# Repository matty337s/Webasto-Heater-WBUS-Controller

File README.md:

# Webasto Heater WBUS Controller

Controller for webasto heater used in vehicles such as Land Rover Discovery 3. Used to turn on and off heater using ATTINY microcontroller, with inputs for USB, ignition and low-beam. Ignition and low-beam inputs can be used to control the heater using the standard vehicle remote control using programmed sequences. PCB designed for Hammond 1551HFLBK enclosure. Software coming soon.

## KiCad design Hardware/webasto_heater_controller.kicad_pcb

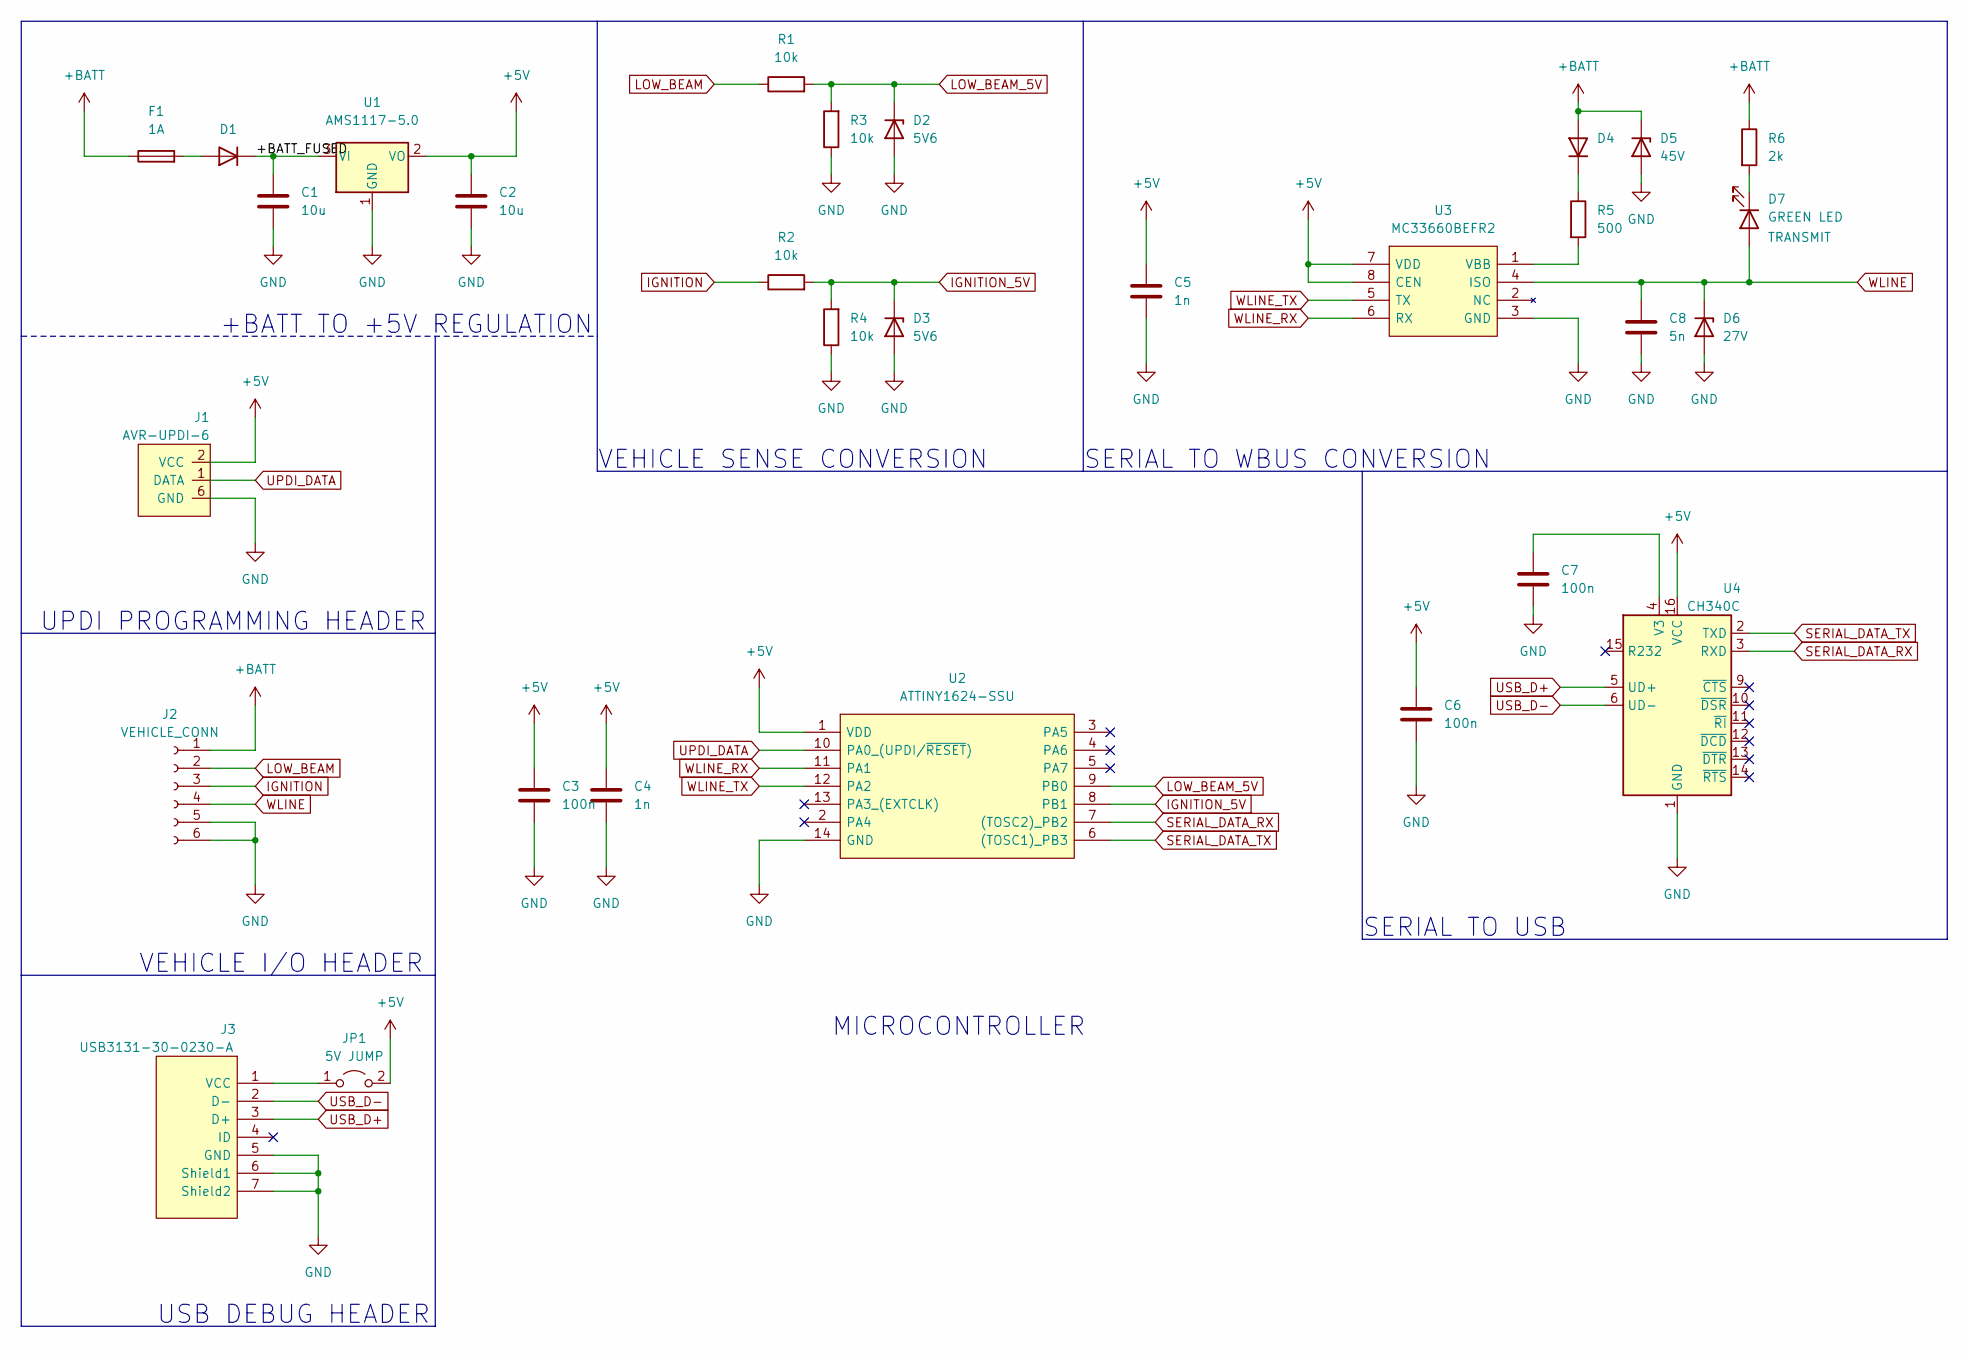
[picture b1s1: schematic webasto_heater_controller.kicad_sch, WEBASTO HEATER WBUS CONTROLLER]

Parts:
C1, C2: 10u; C_0805_2012Metric_Pad1.18x1.45mm_HandSolder
C3, C6, C7: 100n; C_0805_2012Metric_Pad1.18x1.45mm_HandSolder
C4, C5: 1n; C_0805_2012Metric_Pad1.18x1.45mm_HandSolder
C8: 5n; C_0805_2012Metric_Pad1.18x1.45mm_HandSolder
D1, D4: D; D_SOD-323_HandSoldering
D2, D3: 5V6; D_SOD-323_HandSoldering
D5: 45V; D_SOD-323_HandSoldering
D6: 27V; D_SOD-323_HandSoldering
D7: GREEN LED; LED_0805_2012Metric_Pad1.15x1.40mm_HandSolder
F1: 1A; Fuse_0805_2012Metric_Pad1.15x1.40mm_HandSolder
J1: AVR-UPDI-6; PinHeader_2x03_P2.54mm_Vertical
J2: VEHICLE_CONN; PinSocket_1x06_P2.54mm_Horizontal
J3: USB3131-30-0230-A; USB3131300230A; Manufacturer_Part_Number USB3131-30-0230-A; Mouser Part Number 640-USB3131300230A
JP1: 5V JUMP; PinHeader_1x02_P2.54mm_Vertical
R1, R2, R3, R4: 10k; R_0805_2012Metric_Pad1.20x1.40mm_HandSolder
R5: 500; R_0805_2012Metric_Pad1.20x1.40mm_HandSolder
R6: 2k; R_0805_2012Metric_Pad1.20x1.40mm_HandSolder
U1: AMS1117-5.0; SOT-223-3_TabPin2
U2: ATTINY1624-SSU; SOIC127P600X175-14N; Manufacturer_Part_Number ATTINY1624-SSU; Mouser Part Number 556-ATTINY1624-SSU
U3: MC33660BEFR2; SOIC127P600X175-8N; Manufacturer_Part_Number MC33660BEFR2; Mouser Part Number 841-MC33660BEFR2
U4: CH340C; SOIC-16_3.9x9.9mm_P1.27mm

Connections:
+5V: C2.1, C3.1, C4.1, C5.1, C6.1, J1.2 (VCC), JP1.2 (B), U1.2 (VO), U2.1 (VDD), U3.7 (VDD), U3.8 (CEN), U4.16 (VCC)
+BATT: D4.2 (A), D5.1 (K), F1.1, J2.1, R6.1
/+BATT_FUSED: C1.1, D1.1 (K), U1.3 (VI)
GND: C1.2, C2.2, C3.2, C4.2, C5.2, C6.2, C7.2, C8.2, D2.2 (A), D3.2 (A), D5.2 (A), D6.2 (A), J1.6 (GND), J2.5, J2.6, J3.5 (GND), J3.6 (Shield1), J3.7 (Shield2), R3.1, R4.1, U1.1 (GND), U2.14 (GND), U3.3 (GND), U4.1 (GND)
IGNITION: J2.3, R2.1
IGNITION_5V: D3.1 (K), R2.2, R4.2, U2.8 (PB1)
LOW_BEAM: J2.2, R1.1
LOW_BEAM_5V: D2.1 (K), R1.2, R3.2, U2.9 (PB0)
unnamed: C7.1, U4.4 (V3)
unnamed: D1.2 (A), F1.2
unnamed: D4.1 (K), R5.1
unnamed: D7.1 (K), R6.2
unnamed: J3.1 (VCC), JP1.1 (A)
unnamed: R5.2, U3.1 (VBB)
SERIAL_DATA_RX: U2.7 ((TOSC2)_PB2), U4.3 (RXD)
SERIAL_DATA_TX: U2.6 ((TOSC1)_PB3), U4.2 (TXD)
UPDI_DATA: J1.1 (DATA), U2.10 (PA0_(UPDI/~RESET))
USB_D+: J3.3 (D+), U4.5 (UD+)
USB_D-: J3.2 (D-), U4.6 (UD-)
WLINE: C8.1, D6.1 (K), D7.2 (A), J2.4, U3.4 (ISO)
WLINE_RX: U2.11 (PA1), U3.6 (RX)
WLINE_TX: U2.12 (PA2), U3.5 (TX)

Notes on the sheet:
UPDI PROGRAMMING HEADER
+BATT TO +5V REGULATION
SERIAL TO USB
MICROCONTROLLER
USB DEBUG HEADER
VEHICLE I/O HEADER
VEHICLE SENSE CONVERSION
SERIAL TO WBUS CONVERSION

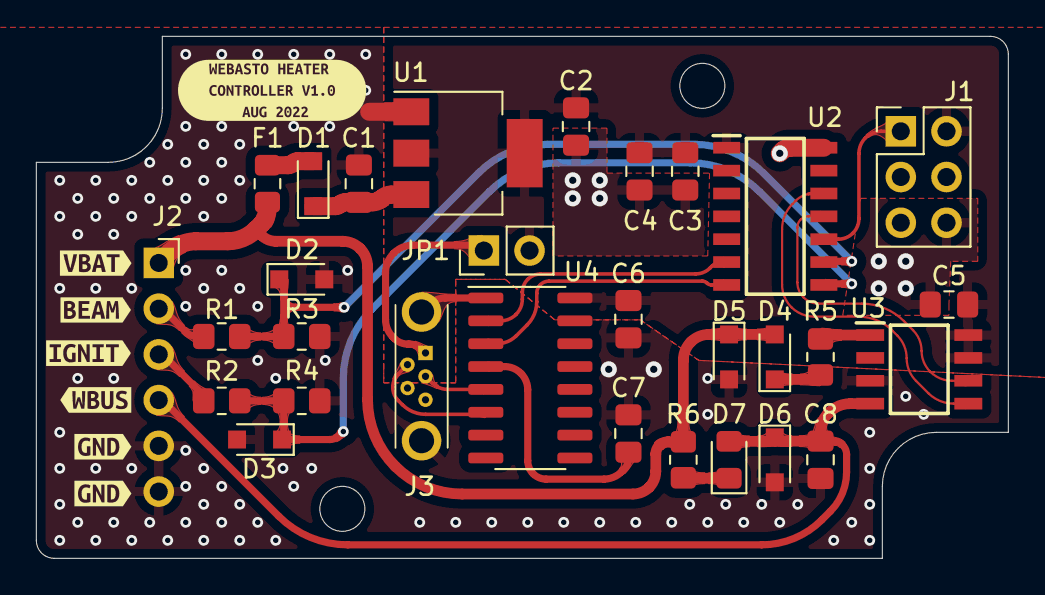
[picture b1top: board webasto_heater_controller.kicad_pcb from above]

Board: 2 copper layers, 54.0 x 29.0 mm, 37 parts (0 on the bottom side), 22 nets.

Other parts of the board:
kibuzzard-62F61DC3: G***; kibuzzard-62F61DC3
kibuzzard-62F61EBF: G***; kibuzzard-62F61EBF
kibuzzard-62F61ED5: G***; kibuzzard-62F61ED5
kibuzzard-62F61EF6: G***; kibuzzard-62F61EF6
kibuzzard-62F61EFB: G***; kibuzzard-62F61EFB
kibuzzard-62F61F6C: G***; kibuzzard-62F61F6C
kibuzzard-62F62203: G***; kibuzzard-62F62203

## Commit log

2022-08-30 Added Images
2022-08-30 Added Schematic
